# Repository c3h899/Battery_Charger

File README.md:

# Battery_Charger
- Battery Charger for (14.4 and 18.0) V NiMH Tool Batteries *Experimental*
- Requires External DC power supply rated for (7.4 to 30) V.
- For best efficiency, avoid Dc supplies in the (18 to 25) V range.

## Revision 4
- Replaced buck converter with LTC3789 Buck-Boost.
- Added isolating resistor R8 between LM7805 and MAX713.
- Provisioned contact sensor and mode switch.

## Revision 3
- Adjusted Footprints.
- Bias network for RV1 adjusted.
- Bleed resistors added to large capacitors.
- Cascode circuitry added to +BATT monitoring to protect MAX713 sense input.
- D2 replaced with Q2 to provide more ideal diode behavior and provide reverse input protection.
- External temperature monitoring circuitry added.
- Low pass RC filters added to +BATT and -BATT sensing pins.
- Reverse input protection added to the DC input and Battery Outputs using P-Channel power MOSFETs.

## Revision 2
- Restructured board to have separate analog and switching ground planes (stared)

## Prototype 0
- Resistor Footprints are WAY too big.
- MAX713 Will regulate voltage across BAT- to BAT+ when measured using resistive load.
- Device successfully achieves current regulation during fast charge.
- At 24 V DC Input the LM7805 Gets hot, may need heatsink.
- Q2 was originally a 1N4001; Replace with 1N5821 due to excessive heating.
- Target Batteries get HOT near end-of charge sequence.
- Device has **NOT** been observed to perform DV/dt charge termination.
- In absence of reverse input protection, installing a charged battery backwards will destroy R7...R10.

## Revision 0
- Design is experimental, based on MAX713 Charge Controller.
- Concept: Replace the Linear Regulated Supply with a Buck Converter.
- Design is intended to charge at C/2 (~1.8 A)
- No use of temperature feedback is employed.
- No effort is made to reverse-input protect board.

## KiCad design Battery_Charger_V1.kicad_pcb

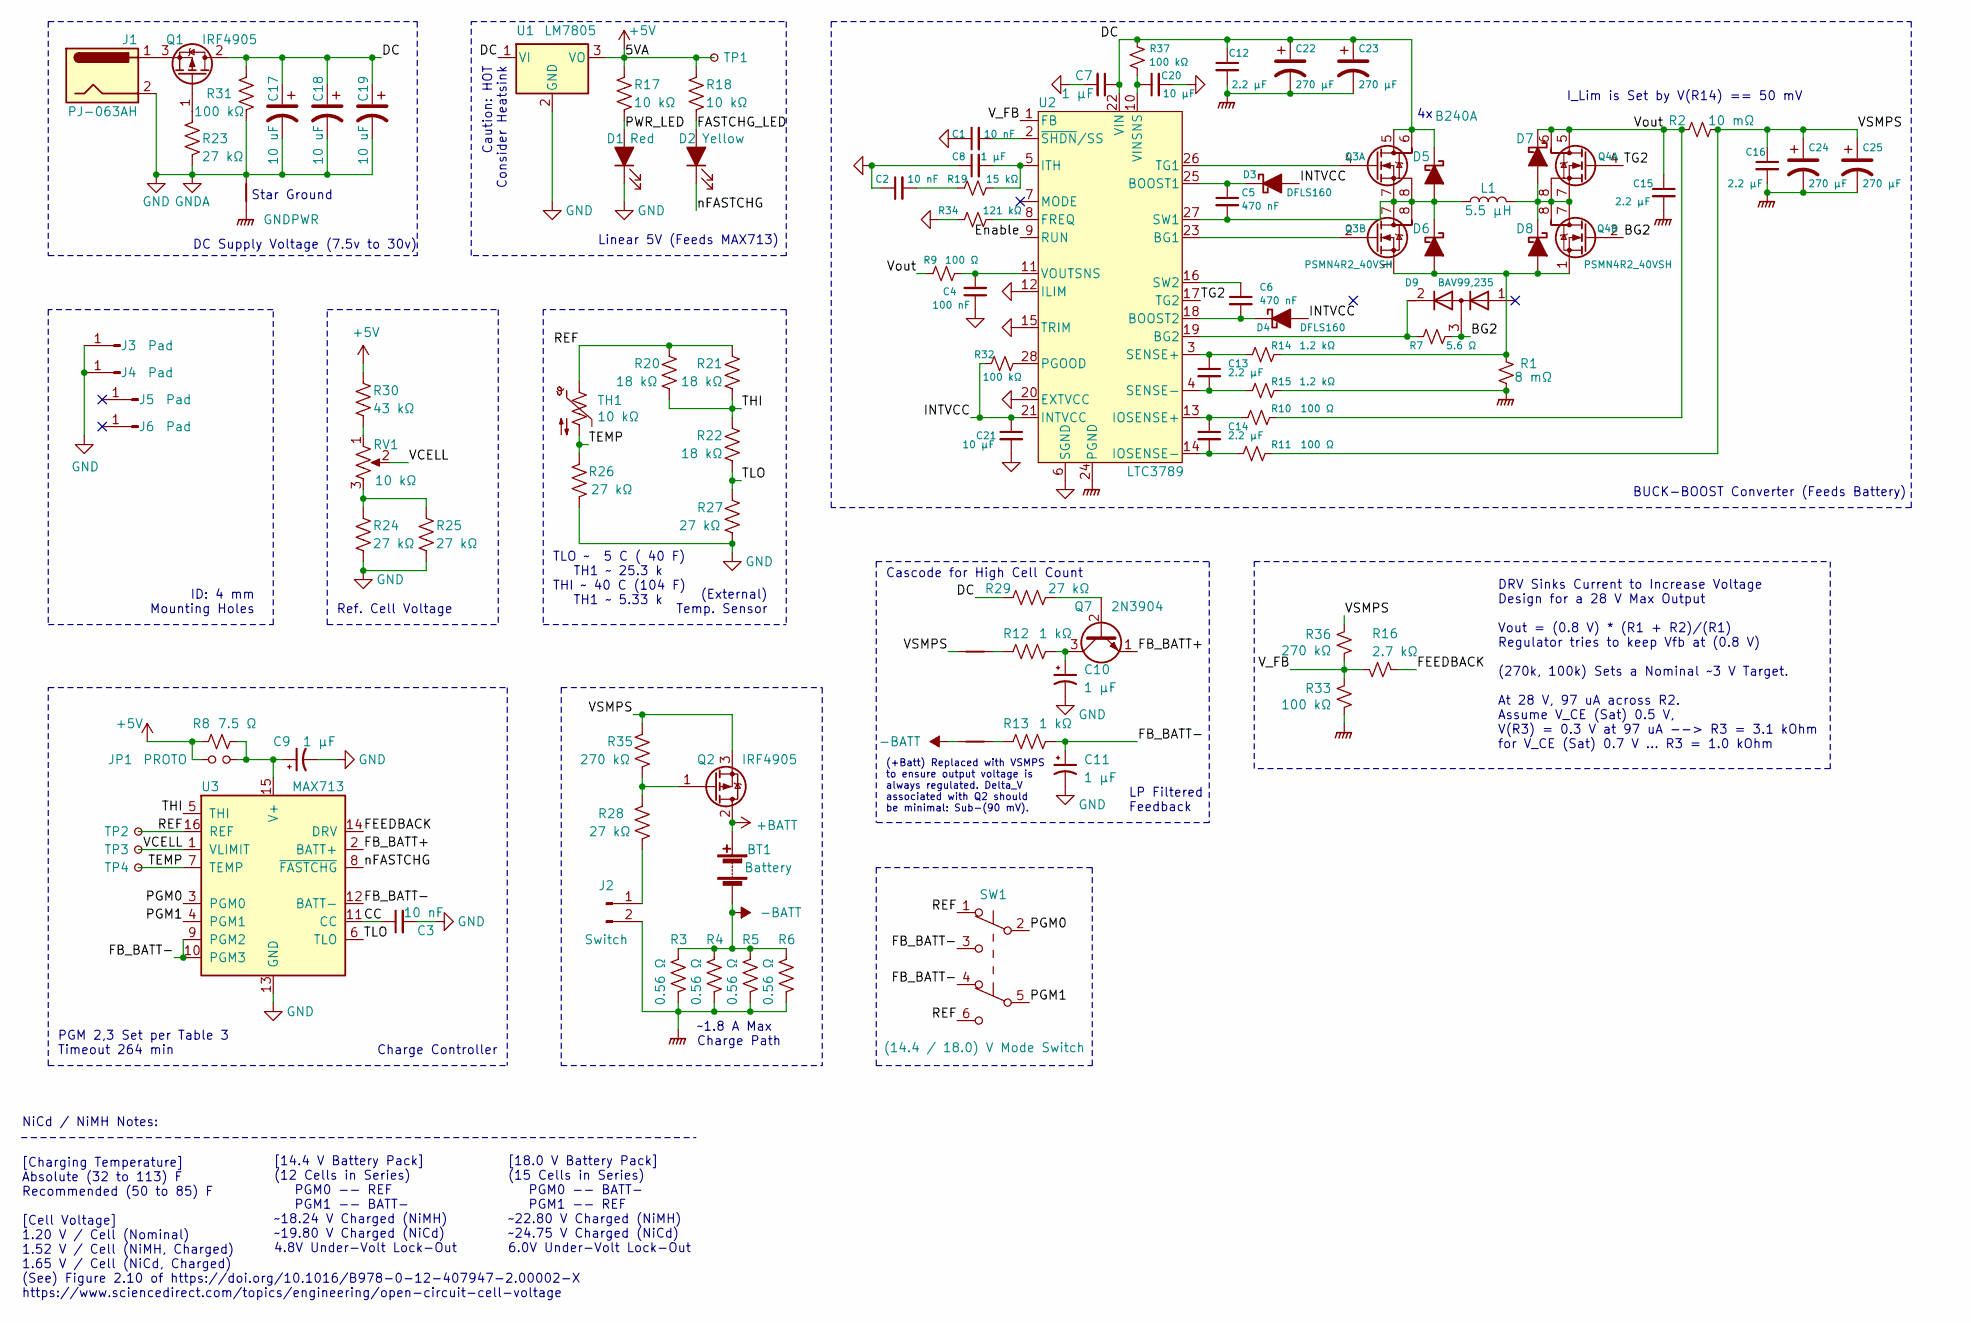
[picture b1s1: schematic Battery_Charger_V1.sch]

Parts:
BT1: Battery; Banana_Jack_2Pin
C1, C2, C3: 10 nF; C_0603_1608Metric_Pad1.08x0.95mm_HandSolder
C4: 100 nF; C_0805_2012Metric_Pad1.18x1.45mm_HandSolder
C5, C6: 470 nF; C_1206_3216Metric_Pad1.33x1.80mm_HandSolder
C7, C8, C9, C10, C11: 1 μF; C_0805_2012Metric_Pad1.18x1.45mm_HandSolder
C12, C13, C14, C15, C16: 2.2 μF; C_1206_3216Metric_Pad1.33x1.80mm_HandSolder
C17, C18, C19: 10 uF; C_1210_3225Metric_Pad1.33x2.70mm_HandSolder
C20, C21: 10 μF; C_1210_3225Metric_Pad1.33x2.70mm_HandSolder
C22, C23, C24, C25: 270 μF; CP_Radial_D10.0mm_P5.00mm
D1: Red; LED_D5.0mm
D2: Yellow; LED_D5.0mm
D3, D4: DFLS160; D_PowerDI-123
D5, D6, D7, D8: B240A; D_SMA-SMB_Universal_Handsoldering
D9: BAV99,235; D_SOT-23_ANK
J1: PJ-063AH; BarrelJack_CUI_PJ-063AH_Horizontal_CircularHoles
J2: Switch; PinHeader_1x02_P2.54mm_Vertical
J3, J4, J5, J6: Pad; TestPoint_Loop_D3.80mm_Drill2.8mm
JP1: PROTO; SolderJumper-2_P1.3mm_Open_Pad1.0x1.5mm
L1: 5.5 μH; 2818
NT1: Net-Tie; NetTie-2_SMD_Pad2.0mm
NT2, NT3: Net-Tie; NetTie-2_SMD_Pad0.5mm
Q1, Q2: IRF4905; TO-220-3_Vertical
Q3, Q4: PSMN4R2_40VSH; LFPAK56D
Q7: 2N3904; TO-92_Inline
R1: 8 mΩ; R_0805_2012Metric_Pad1.20x1.40mm_HandSolder
R2: 10 mΩ; R_0805_2012Metric_Pad1.20x1.40mm_HandSolder
R3, R4, R5, R6: 0.56 Ω; R_Axial_DIN0617_L17.0mm_D6.0mm_P20.32mm_Horizontal
R7: 5.6 Ω; R_0805_2012Metric_Pad1.20x1.40mm_HandSolder
R8: 7.5 Ω; R_0805_2012Metric_Pad1.20x1.40mm_HandSolder
R9, R10, R11: 100 Ω; R_0805_2012Metric_Pad1.20x1.40mm_HandSolder
R12, R13: 1 kΩ; R_0805_2012Metric_Pad1.20x1.40mm_HandSolder
R14, R15: 1.2 kΩ; R_0805_2012Metric_Pad1.20x1.40mm_HandSolder
R16: 2.7 kΩ; R_0805_2012Metric_Pad1.20x1.40mm_HandSolder
R17, R18: 10 kΩ; R_0805_2012Metric_Pad1.20x1.40mm_HandSolder
R19: 15 kΩ; R_0805_2012Metric_Pad1.20x1.40mm_HandSolder
R20, R21, R22: 18 kΩ; R_0805_2012Metric_Pad1.20x1.40mm_HandSolder
R23, R24, R25, R26, R27, R28, R29: 27 kΩ; R_0805_2012Metric_Pad1.20x1.40mm_HandSolder
R30: 43 kΩ; R_0805_2012Metric_Pad1.20x1.40mm_HandSolder
R31, R32, R33, R37: 100 kΩ; R_0805_2012Metric_Pad1.20x1.40mm_HandSolder
R34: 121 kΩ; R_0805_2012Metric_Pad1.20x1.40mm_HandSolder
R35, R36: 270 kΩ; R_0805_2012Metric_Pad1.20x1.40mm_HandSolder
RV1: 10 kΩ; Potentiometer_Bourns_PTV09A-1_Single_Vertical
SW1: (14.4 / 18.0) V Mode Switch; DPDT
TH1: 10 kΩ; PinHeader_1x02_P2.54mm_Vertical
TP1, TP2, TP3, TP4: TestPoint_Small; TestPoint_Pad_2.5x2.5mm
U1: LM7805; TO-220-3_Vertical
U2: LTC3789; SSOP-28_3.9x9.9mm_P0.635mm
U3: MAX713; SOIC-16_4.55x10.3mm_P1.27mm

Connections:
+5V: JP1.1, R8.2, R17.2, R18.2, R30.1, TP1.1, U1.3 (VO)
+BATT: BT1.1 (+), Q2.2 (D)
-BATT: BT1.2 (-), NT3.1, R3.1, R4.1, R5.1, R6.1
/BG2: D9.3 (common), Q4.2 (G2), R7.1
/CC: C3.1, U3.11 (CC)
/DC: C7.1, C12.1, C17.1, C18.1, C19.1, C22.1, C23.1, D5.1 (K), Q1.2 (D), Q3.5 (D1), Q3.6 (D1), R29.2, R31.2, R37.2, U1.1 (VI), U2.22 (VIN)
/Enable: U2.9 (RUN)
/FASTCHG_LED: D2.2 (A), R18.1
/FB_BATT+: Q7.1 (E), U3.2 (BATT+)
/FB_BATT-: C11.1, R13.1, SW1.3 (C), SW1.4 (A), U3.9 (PGM2), U3.10 (PGM3), U3.12 (BATT-)
/FEEDBACK: R16.1, U3.14 (DRV)
/INTVCC: C21.1, D3.2 (A), D4.2 (A), R32.2, U2.21 (INTVCC)
/PGM0: SW1.2 (B), U3.3 (PGM0)
/PGM1: SW1.5 (B), U3.4 (PGM1)
/PWR_LED: D1.2 (A), R17.1
/REF: R20.1, R21.2, SW1.1 (A), SW1.6 (C), TH1.1, TP2.1, U3.16 (REF)
/TEMP: R26.1, TH1.2, TP4.1, U3.7 (TEMP)
/TG2: Q4.4 (G1), U2.17 (TG2)
/THI: R20.2, R21.1, R22.2, U3.5 (THI)
/TLO: R22.1, R27.1, U3.6 (TLO)
/VCELL: RV1.2, TP3.1, U3.1 (VLIMIT)
/VSMPS: C16.1, C24.1, C25.1, NT2.1, Q2.3 (S), R2.2, R11.1, R35.2, R36.1
/V_FB: R16.2, R33.1, R36.2, U2.1 (FB)
/Vout: C15.1, D7.1 (K), Q4.5 (D1), Q4.6 (D1), R2.1, R9.2, R10.1
/nFASTCHG: D2.1 (K), U3.8 (~FASTCHG)
GND: C1.1, C2.1, C3.2, C4.1, C7.2, C8.1, C9.2, C10.2, C11.2, C17.2, C18.2, C19.2, C20.2, C21.2, D1.1 (K), J1.2, J3.1, J4.1, NT1.1, R23.1, R24.2, R25.2, R26.2, R27.2, R31.1, R34.2, SW1.0, U1.2 (GND), U2.6 (SGND), U2.12 (ILIM), U2.15 (TRIM), U2.20 (EXTVCC), U3.13 (GND)
GNDPWR: C12.2, C15.2, C16.2, C22.2, C23.2, C24.2, C25.2, J2.2, NT1.2, R1.1, R3.2, R4.2, R5.2, R6.2, R15.1, R33.2, U2.24 (PGND)
unnamed: C1.2, U2.2 (~SHDN~/SS)
unnamed: C2.2, R19.2
unnamed: C4.2, R9.1, U2.11 (VOUTSNS)
unnamed: C5.1, D3.1 (K), U2.25 (BOOST1)
unnamed: C5.2, D5.2 (A), D6.1 (K), L1.1, Q3.7 (S1), Q3.8 (S1), U2.27 (SW1)
unnamed: C6.1, U2.16 (SW2)
unnamed: C6.2, D4.1 (K), U2.18 (BOOST2)
unnamed: C8.2, R19.1, U2.5 (ITH)
unnamed: C9.1, JP1.2, R8.1, U3.15 (V+)
unnamed: C10.1, Q7.3 (C), R12.1
unnamed: C13.1, R14.2, U2.3 (SENSE+)
unnamed: C13.2, R15.2, U2.4 (SENSE-)
unnamed: C14.1, R10.2, U2.13 (IOSENSE+)
unnamed: C14.2, R11.2, U2.14 (IOSENSE-)
unnamed: C20.1, R37.1, U2.10 (VINSNS)
unnamed: D6.2 (A), D8.2 (A), Q3.1 (S2), Q4.1 (S2), R1.2, R14.1
unnamed: D7.2 (A), D8.1 (K), L1.2, Q4.7 (S1), Q4.8 (S1)
unnamed: D9.2 (K), R7.2, U2.19 (BG2)
unnamed: J1.1, Q1.3 (S)
unnamed: J2.1, R28.1
unnamed: NT2.2, R12.2
unnamed: NT3.2, R13.2
unnamed: Q1.1 (G), R23.2
unnamed: Q2.1 (G), R28.2, R35.1
unnamed: Q3.2 (G2), U2.23 (BG1)
unnamed: Q3.4 (G1), U2.26 (TG1)
unnamed: Q7.2 (B), R29.1
unnamed: R24.1, R25.1, RV1.3
unnamed: R30.2, RV1.1
unnamed: R32.1, U2.28 (PGOOD)
unnamed: R34.1, U2.8 (FREQ)

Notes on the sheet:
Star Ground
I_Lim is Set by V(R14) == 50 mV
DRV Sinks Current to Increase Voltage Design for a 28 V Max Output Vout = (0.8 V) * (R1 + R2)/(R1) Regulator tries to keep Vfb at (0.8 V) (270k, 100k) Sets a Nominal ~~3 V Target. At 28 V, 97 uA across R2. Assume V_CE (Sat) 0.5 V, V(R3) = 0.3 V at 97 uA --> R3 = 3.1 kOhm for V_CE (Sat) 0.7 V ... R3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
[14.4 V Battery Pack] (12 Cells in Series) PGM0 -- REF PGM1 -- BATT- ~~18.24 V Charged (NiMH) ~~19.80 V Charged (NiCd) 4.8V Under-Volt Lock-Out
NiCd / NiMH Notes:
BUCK-BOOST Converter (Feeds Battery)
[Charging Temperature] Absolute (32 to 113) F Recommended (50 to 85) F [Cell Voltage] 1.20 V / Cell (Nominal) 1.52 V / Cell (NiMH, Charged) 1.65 V / Cell (NiCd, Charged) (See) Figure 2.10 of https://doi.org/10.1016/B978-0-12-407947-2.00002-X https://www.sciencedirect.com/topics/engineering/open-cir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
DC Supply Voltage (7.5v to 30v)
Linear 5V (Feeds MAX713)
ID: 4 mm Mounting Holes
(External) Temp. Sensor
Ref. Cell Voltage
Charge Controller
[18.0 V Battery Pack] (15 Cells in Series) PGM0 -- BATT- PGM1 -- REF ~~22.80 V Charged (NiMH) ~~24.75 V Charged (NiCd) 6.0V Under-Volt Lock-Out
Caution: HOT Consider Heatsink
TLO ~~ 5 C ( 40 F) TH1 ~~ 25.3 k THI ~~ 40 C (104 F) TH1 ~~ 5.33 k
Cascode for High Cell Count
LP Filtered Feedback
~~1.8 A Max Charge Path
PGM 2,3 Set per Table 3 Timeout 264 min
(+Batt) Replaced with VSMPS to ensure output voltage is always regulated. Delta_V associated with Q2 should be minimal: Sub-(90 mV).

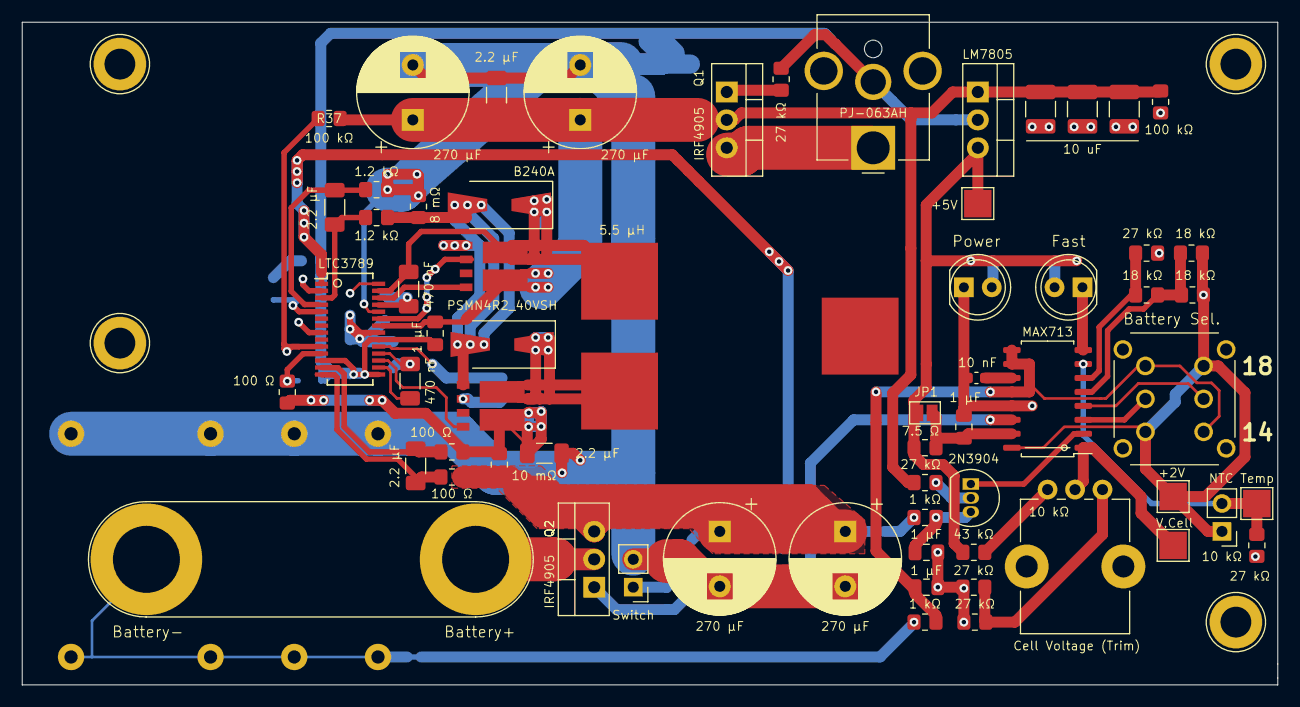
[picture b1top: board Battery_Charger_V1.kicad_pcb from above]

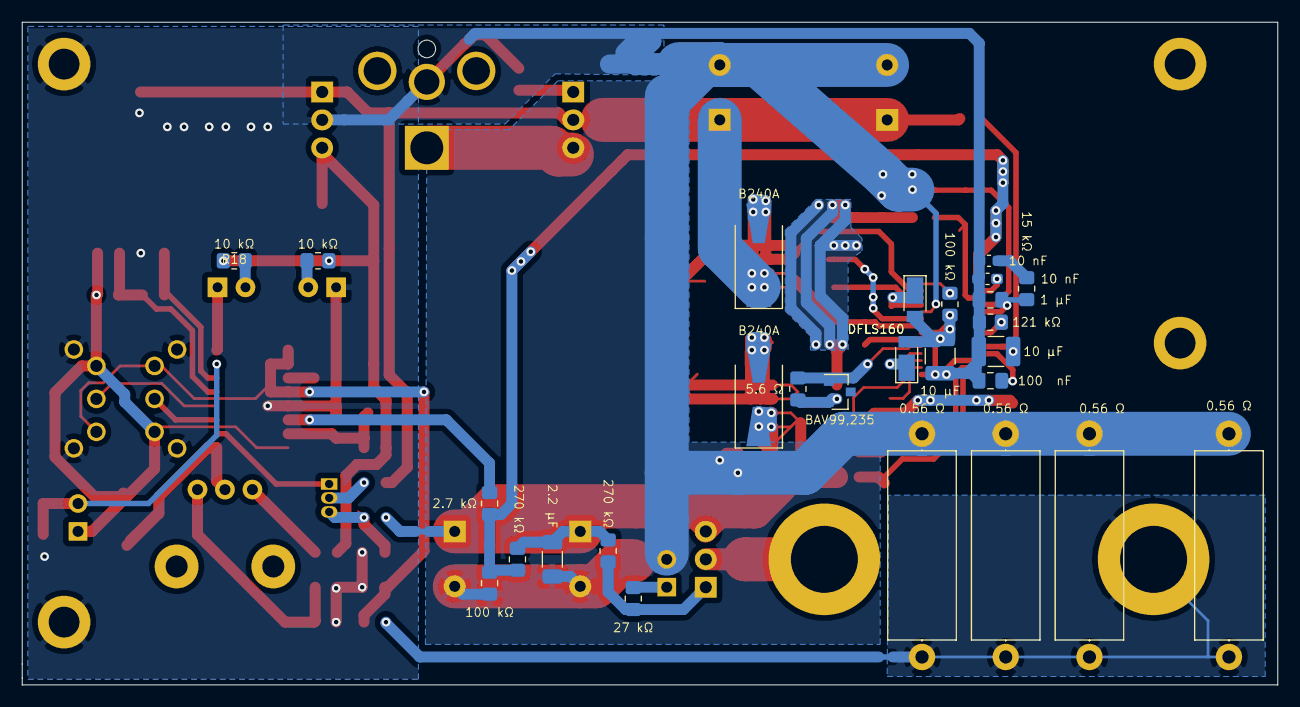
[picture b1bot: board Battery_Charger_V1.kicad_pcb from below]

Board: 2 copper layers, 114.3 x 60.3 mm, 98 parts (30 on the bottom side), 57 nets.

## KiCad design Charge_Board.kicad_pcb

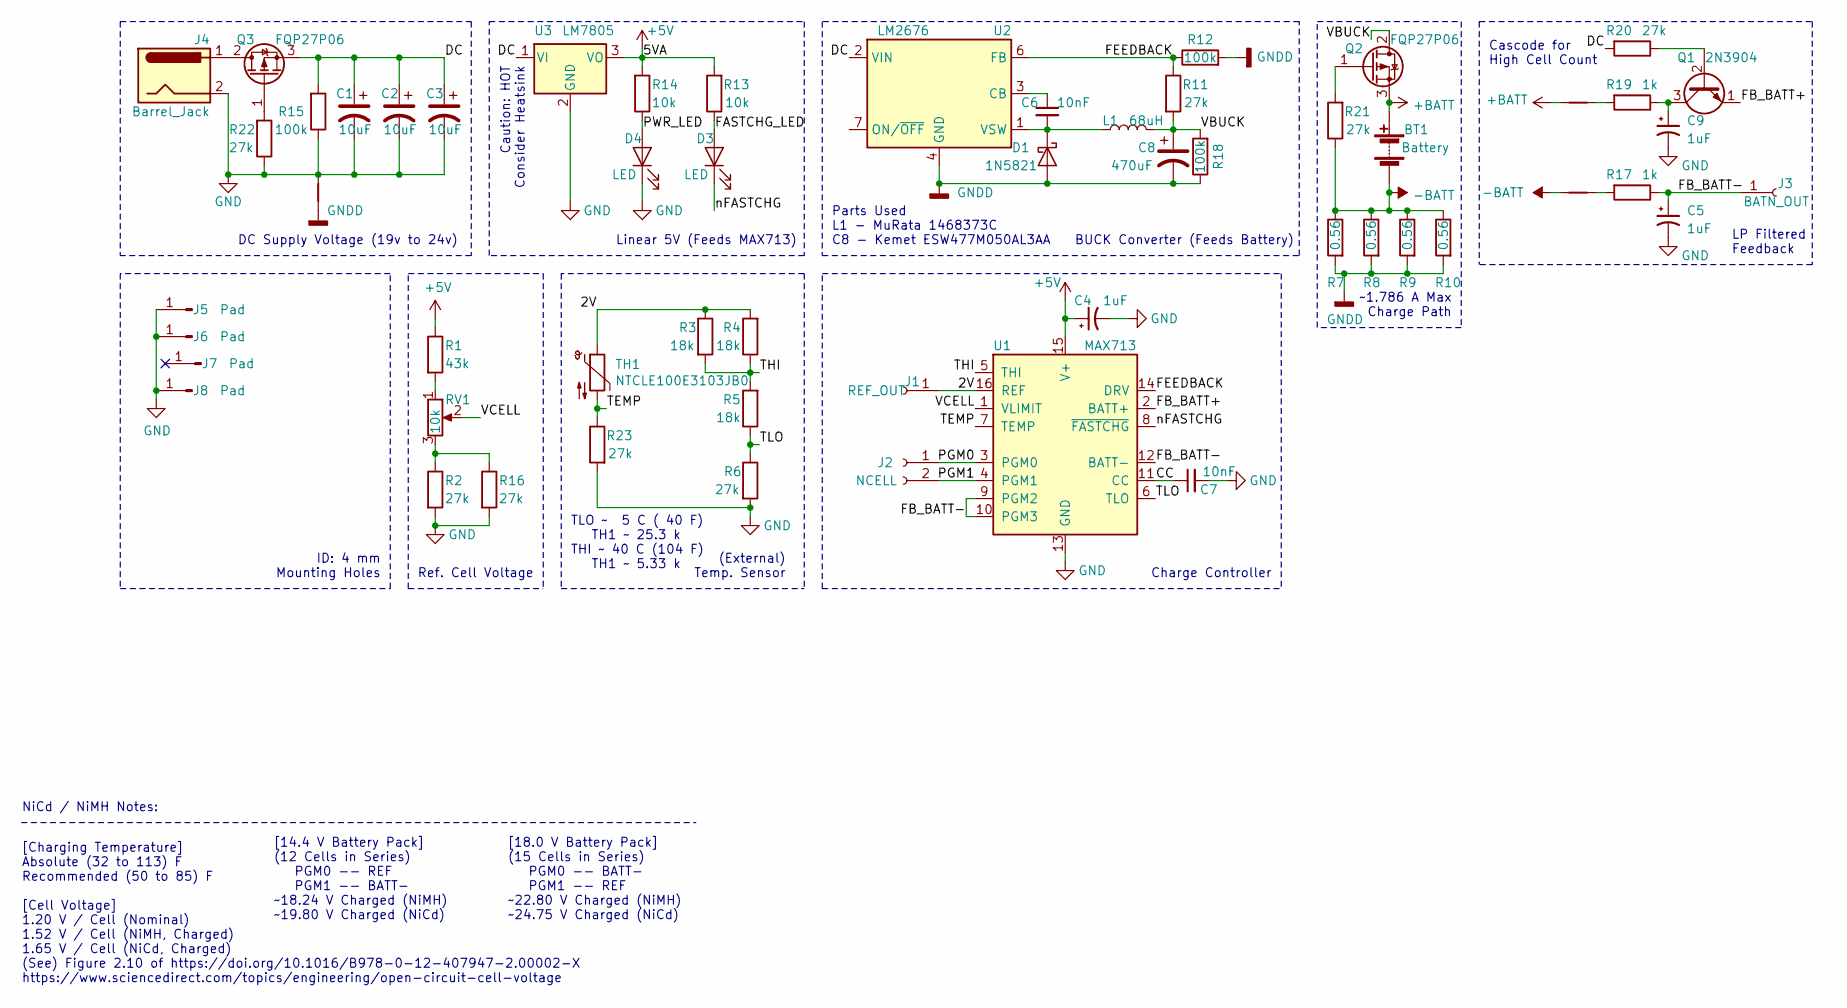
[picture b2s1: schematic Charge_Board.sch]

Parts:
BT1: Battery; Banana_Jack_2Pin
C1, C2, C3: 10uF; CP_Radial_D6.3mm_P2.50mm
C4, C5, C9: 1uF; CP_Radial_D5.0mm_P2.00mm
C6, C7: 10nF; C_Rect_L4.0mm_W2.5mm_P2.50mm
C8: 470uF; CP_Radial_D14.0mm_P5.00mm
D1: 1N5821; D_DO-201AD_P12.70mm_Horizontal
D3, D4: LED; LED_D5.0mm
J1: REF_OUT; PinHeader_1x01_P2.54mm_Vertical
J2: NCELL; PinHeader_1x02_P2.54mm_Vertical
J3: BATN_OUT; PinHeader_1x01_P2.54mm_Vertical
J4: Barrel_Jack; BarrelJack_CUI_PJ-102AH_Horizontal
J5, J6, J7, J8: Pad; Banana_Jack_1Pin
L1: 68uH; L_Radial_D24.4mm_P23.90mm_muRATA_1400series
NT1: Net-Tie; NetTie-2_SMD_Pad2.0mm
NT2, NT3: Net-Tie; NetTie-2_SMD_Pad0.5mm
Q1: 2N3904; TO-92_Inline
Q2, Q3: FQP27P06; TO-220-3_Vertical
R1: 43k; R_Axial_DIN0207_L6.3mm_D2.5mm_P10.16mm_Horizontal
R2, R6, R11, R16, R20, R21, R22, R23: 27k; R_Axial_DIN0207_L6.3mm_D2.5mm_P10.16mm_Horizontal
R3, R4, R5: 18k; R_Axial_DIN0207_L6.3mm_D2.5mm_P10.16mm_Horizontal
R7, R8, R9, R10: 0.56; R_Axial_DIN0309_L9.0mm_D3.2mm_P12.70mm_Horizontal
R12, R15, R18: 100k; R_Axial_DIN0207_L6.3mm_D2.5mm_P10.16mm_Horizontal
R13, R14: 10k; R_Axial_DIN0207_L6.3mm_D2.5mm_P10.16mm_Horizontal
R17, R19: 1k; R_Axial_DIN0207_L6.3mm_D2.5mm_P10.16mm_Horizontal
RV1: 10k; Potentiometer_Bourns_PTV09A-1_Single_Vertical
TH1: NTCLE100E3103JB0; PinHeader_1x02_P2.54mm_Vertical
U1: MAX713; SOIC-16_4.55x10.3mm_P1.27mm
U2: LM2676; TO-263-7_TabPin8
U3: LM7805; TO-220-3_Vertical

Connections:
+5V: C4.1, R1.1, R13.2, R14.2, U1.15 (V+), U3.3 (VO)
+BATT: BT1.1 (+), NT2.1, Q2.3 (S)
-BATT: BT1.2 (-), NT3.1, R7.1, R8.1, R9.1, R10.1, R21.1
/2V: J1.1, R3.1, R4.2, TH1.1, U1.16 (REF)
/CC: C7.1, U1.11 (CC)
/DC: C1.1, C2.1, C3.1, Q3.3 (S), R15.2, R20.2, U2.2 (VIN), U3.1 (VI)
/FASTCHG_LED: D3.2 (A), R13.1
/FB_BATT+: Q1.1 (E), U1.2 (BATT+)
/FB_BATT-: C5.1, J3.1, R17.1, U1.9 (PGM2), U1.10 (PGM3), U1.12 (BATT-)
/FEEDBACK: R11.1, R12.1, U1.14 (DRV), U2.6 (FB)
/PGM0: J2.1, U1.3 (PGM0)
/PGM1: J2.2, U1.4 (PGM1)
/PWR_LED: D4.2 (A), R14.1
/TEMP: R23.1, TH1.2, U1.7 (TEMP)
/THI: R3.2, R4.1, R5.2, U1.5 (THI)
/TLO: R5.1, R6.1, U1.6 (TLO)
/VBUCK: C8.1, L1.2, Q2.2 (D), R11.2, R18.2
/VCELL: RV1.2, U1.1 (VLIMIT)
/nFASTCHG: D3.1 (K), U1.8 (~FASTCHG)
GND: C1.2, C2.2, C3.2, C4.2, C5.2, C7.2, C9.2, D4.1 (K), J4.2, J5.1, J6.1, J8.1, NT1.1, R2.2, R6.2, R15.1, R16.2, R22.1, R23.2, U1.13 (GND), U3.2 (GND)
GNDD: C8.2, D1.2 (A), NT1.2, R7.2, R8.2, R9.2, R10.2, R12.2, R18.1, U2.4 (GND), U2.8
unnamed: C6.1, U2.3 (CB)
unnamed: C6.2, D1.1 (K), L1.1, U2.1 (VSW)
unnamed: C9.1, Q1.3 (C), R19.1
unnamed: J4.1, Q3.2 (D)
unnamed: NT2.2, R19.2
unnamed: NT3.2, R17.2
unnamed: Q1.2 (B), R20.1
unnamed: Q2.1 (G), R21.2
unnamed: Q3.1 (G), R22.2
unnamed: R1.2, RV1.1
unnamed: R2.1, R16.1, RV1.3

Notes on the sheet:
[14.4 V Battery Pack] (12 Cells in Series) PGM0 -- REF PGM1 -- BATT- ~~18.24 V Charged (NiMH) ~~19.80 V Charged (NiCd)
Parts Used L1 - MuRata 1468373C C8 - Kemet ESW477M050AL3AA
NiCd / NiMH Notes:
~~1.786 A Max Charge Path
BUCK Converter (Feeds Battery)
LP Filtered Feedback
[Charging Temperature] Absolute (32 to 113) F Recommended (50 to 85) F [Cell Voltage] 1.20 V / Cell (Nominal) 1.52 V / Cell (NiMH, Charged) 1.65 V / Cell (NiCd, Charged) (See) Figure 2.10 of https://doi.org/10.1016/B978-0-12-407947-2.00002-X https://www.sciencedirect.com/topics/engineering/open-cir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
DC Supply Voltage (19v to 24v)
Linear 5V (Feeds MAX713)
ID: 4 mm Mounting Holes
(External) Temp. Sensor
Ref. Cell Voltage
Charge Controller
Cascode for High Cell Count
[18.0 V Battery Pack] (15 Cells in Series) PGM0 -- BATT- PGM1 -- REF ~~22.80 V Charged (NiMH) ~~24.75 V Charged (NiCd)
Caution: HOT Consider Heatsink
TLO ~~ 5 C ( 40 F) TH1 ~~ 25.3 k THI ~~ 40 C (104 F) TH1 ~~ 5.33 k

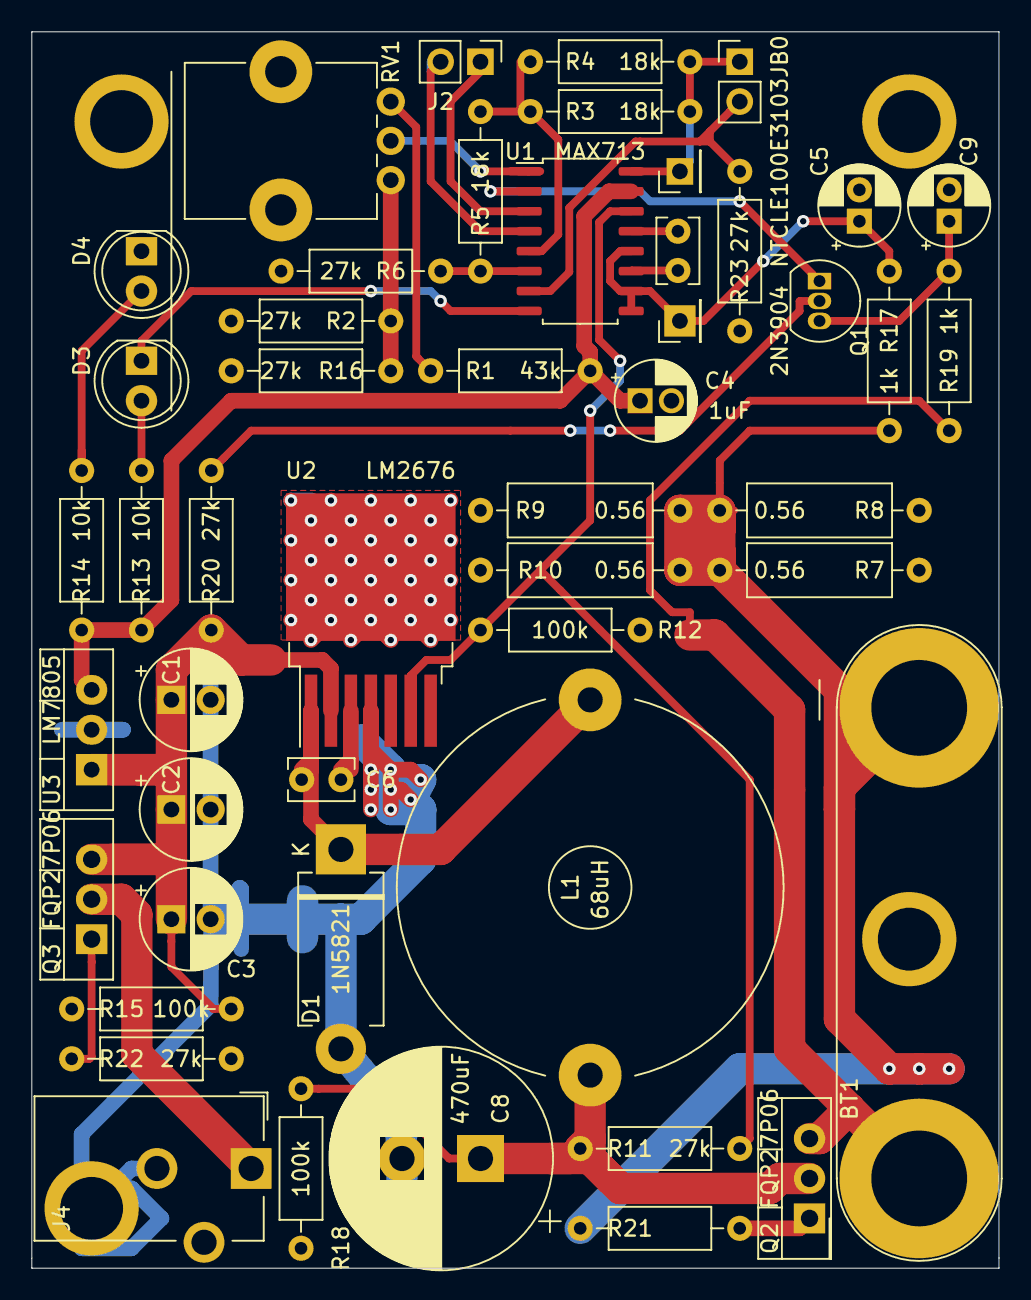
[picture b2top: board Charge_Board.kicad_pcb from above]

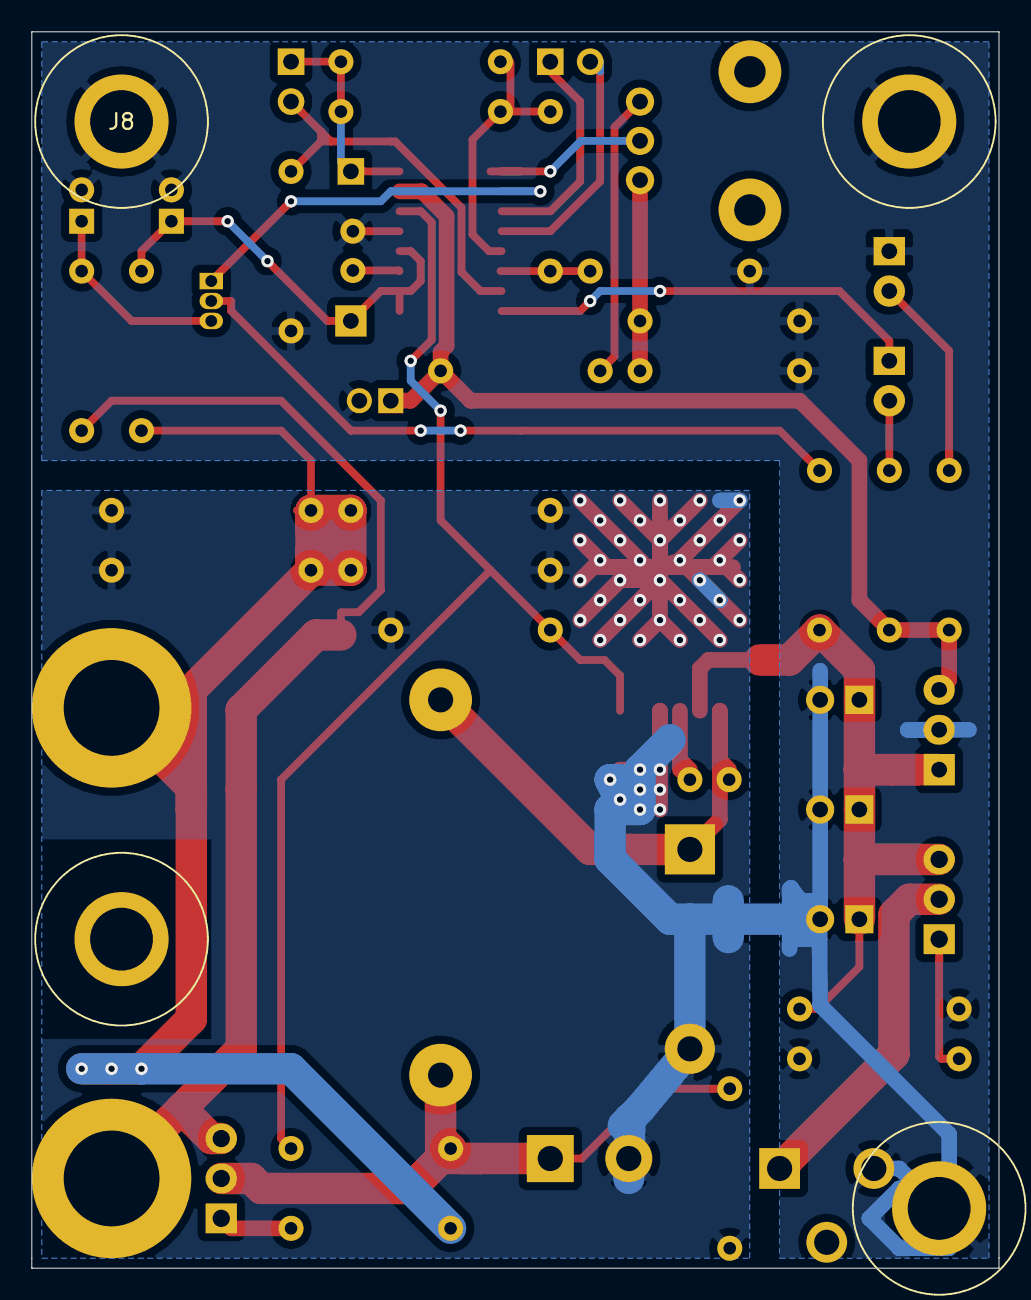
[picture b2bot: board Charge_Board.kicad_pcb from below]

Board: 2 copper layers, 61.6 x 78.7 mm, 56 parts (5 on the bottom side), 32 nets.

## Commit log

2020-04-18 Initial Upload of Designs
2020-04-18 Images.
2020-04-18 Added BOM
2022-11-10 Updated Design
    Reverted to MAX713 controller.
    Design is (Mostly) a direct iteration on the master branch.
    TODO: Review MAX713 behavior in presence of damaged cells.
2022-11-13 Schematic Revision
    Added a mode switch for improved end-user experience.
2022-11-13 Corrected Q1
    P-Channel MOSFET was oriented incorrectly.
2022-11-17 Draft PCB
    Minor edits to schematic.
    PCB is **NOT** fully routed.
2022-11-18 Draft PCB(2)
    Incomplete
    Routing has begun to consider current associated with circuit traces.
2022-11-19 Draft PCB(3)
    Pre-DRC
2022-12-05 Revised Switch Footprint
